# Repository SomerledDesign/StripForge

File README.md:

# StripForge

**Lay out stripboard (Veroboard) circuits in KiCad with real footprints and a live netlist, and get a normal `.kicad_pcb` whose copper is the strips.**

> **Beta (0.3.0).** KiCad 10 only. So far it has been tested on one real board (an ATtiny10
> programming fixture on a 24 × 56 hole stripboard). It works well there, but expect rough
> edges on other boards. Keep backups, check the DRC, and please report what you find.

## Why

Stripboard is still the quickest way to build a one-off circuit you can solder, but laying it out
usually means leaving KiCad for a separate app with its own parts and its own idea of the circuit.
Then the schematic and the build drift apart.

StripForge keeps the whole job inside KiCad:

- **Real KiCad footprints.** It uses the parts from your project, not a second parts library.
- **A live netlist.** The schematic stays the source of truth, and KiCad's schematic-parity check
  keeps the board honest.
- **A normal `.kicad_pcb` as output.** The copper is stripboard strips on B.Cu instead of routed
  tracks. You can open, edit, DRC and plot it like any other board.
- **A printable build sheet.** The copper side mirrored the way you hold the board to cut it, with
  every cut, link and part in checklists.

## What it does

1. **Snaps parts to the grid.** Place the through-hole parts roughly on a 2.54 mm (0.1") grid.
   StripForge snaps each footprint to the nearest holes and logs anything that is off.
2. **Splits the strips by net.** Wherever two nets would share a strip, it cuts the strip. A cut is
   a real gap in the copper plus a `CUT` marker you can see and move.
3. **Adds wire links.** Pieces of one net on different strips are joined with wire links (`W1`,
   `W2`, …), placed on their holes. Links are also added to the schematic, so the two stay in
   sync.
4. **Checks the result with KiCad's DRC**, including schematic parity: a strip carrying two nets, a
   missing link or an extra cut shows up as an error.
5. **Writes a build sheet** (HTML, and PDF when Chrome is installed).

| KiCad's copper layer after Build strips (B.Cu, mirrored) | The build sheet's component side |
|---|---|
|  |  |

The full design is in [Sketch.md](Sketch.md).

## Install

StripForge is a KiCad 10 **IPC plugin**. It is not in KiCad's official Plugin and Content Manager
(PCM) yet.

1. KiCad > Preferences > Plugins: tick **Enable KiCad API**, and check that the Python interpreter
   is KiCad's own (the default on macOS).
2. Build both packages with `python tools/make_pcm_zip.py` (they land in `dist/`), or take them
   from a release. KiCad's addon guide wants a plugin package and a library package, not one zip
   of both. In the Plugin and Content Manager, click **Install from File…** and install
   `StripForge-libraries-0.3.0-pcm.zip` first, then `StripForge-0.3.0-pcm.zip`:

   StripForge then shows on the **Installed** tab as version 0.3.0:

3. **Restart KiCad.** The first time you open a board, KiCad sets up the plugin's Python
   environment, which takes a minute. The PCB editor toolbar shows one button, **Dialog**. It
   opens the window with the Board and Backup tabs. Analyze, Build strips, Add links, Run DRC,
   Build sheet and Restore last are buttons in that window. The Report wraps long lines.

   The picture below is from 0.2.x, when the toolbar had a button per action. 0.3.0 does not.

4. **Check the footprint and symbol libraries.** KiCad's manual says a library package is added
   to the global tables, and the default nickname prefix is `PCM_`. This was not clicked in KiCad
   here, so look at Preferences > Manage Footprint Libraries and Manage Symbol Libraries. If rows
   appeared, they are named `PCM_StripForge`. Rename each to `StripForge` so it matches the
   `StripForge:Link_*` footprints and the `StripForge:Link` symbol the build writes. If no row
   appeared, add them with nickname `StripForge` and these paths:

   - Footprints: `${KICAD10_3RD_PARTY}/footprints/com_github_somerleddesign_stripforge_libraries/StripForge.pretty`
   - Symbols: `${KICAD10_3RD_PARTY}/symbols/com_github_somerleddesign_stripforge_libraries/StripForge.kicad_sym`
   - 3D models (no library table): `${KICAD10_3RD_PARTY}/3dmodels/com_github_somerleddesign_stripforge_libraries/StripForge.3dshapes`

   Each straight `Link_P*` footprint names the matching `.step` in that 3D folder. The `.wrl` has
   the same name beside it. A new straight link copies the footprint, so it inherits that model.
   Diagonal links and the cut markers have no model. The plugin also keeps a private copy of the
   footprints so it can build without the library table. The 3D files themselves are only in the
   libraries package. **Update Footprints from Library**, the 3D viewer, and placing a link by
   hand use the library-table row.

To install by hand instead, copy the *contents* of the plugin zip's `plugins/` folder to
`~/Documents/KiCad/10.0/3rdparty/plugins/com_github_somerleddesign_stripforge/` (macOS; on Linux
`~/.local/share/kicad/10.0/3rdparty/plugins/`, on Windows
`Documents\KiCad\10.0\3rdparty\plugins\`). From the libraries zip, copy
`footprints/StripForge.pretty` to
`.../3rdparty/footprints/com_github_somerleddesign_stripforge_libraries/StripForge.pretty`,
`symbols/StripForge.kicad_sym` to
`.../3rdparty/symbols/com_github_somerleddesign_stripforge_libraries/StripForge.kicad_sym`, and
`3dmodels/StripForge.3dshapes` to
`.../3rdparty/3dmodels/com_github_somerleddesign_stripforge_libraries/StripForge.3dshapes`.
Add the footprint and symbol libraries with nickname `StripForge`. To update, install both new
zips the same way and restart KiCad. If a button does nothing, try Preferences > Plugins >
**Recreate Plugin Environment**.

### If the buttons don't appear (Linux)

On Debian and Ubuntu, KiCad builds the plugin's Python environment with the system Python, which
needs the `python3-venv` package. If that package was missing the first time KiCad tried, it leaves
a half-built environment with no pip, and it keeps reusing it even after you install
`python3-venv`. KiCad prints no error for this, and StripForge never shows up. To fix it:

1. Close KiCad.
2. Install the venv package: `sudo apt install python3-venv`.
3. Delete the broken environment:
   `rm -rf ~/.cache/kicad/10.0/python-environments/com.github.somerleddesign.stripforge`
4. Open the PCB editor again and give it a few seconds to install. The Dialog button appears at the
   right end of the top toolbar.

(The folder is `~/.cache/kicad/10.0/python-environments/` on a standard Linux install; check the
exact name and case with `ls ~/.cache | grep -i kicad` if yours differs. On macOS it is
`~/Library/Caches/KiCad/10.0/python-environments/com.github.somerleddesign.stripforge`; macOS
file names are case-insensitive, so the case doesn't matter there.)

### NixOS, or no dialogs (only status-bar warnings)

StripForge's dialogs need wxPython in the plugin's environment. On NixOS (and any Python without
wxPython) the buttons run but every message only reaches the PCB editor's status-bar warnings; the
full report is still in `stripforge/<Project>-stripforge.log`, and Build strips refuses to
write into the board without a dialog to confirm it. To fix it, set Preferences > Plugins >
**Python interpreter** to a Python that has wxPython (on NixOS, one whose packages include
`wxpython`), then **Recreate Plugin Environment** and restart KiCad.

StripForge isn't listed under Tools > External Plugins, because that menu is for the older SWIG
plugins; the Dialog toolbar button is where it lives. If it still doesn't load, start the PCB editor from
a terminal with `KICAD_ENABLE_WXTRACE=1 WXTRACE=KICAD_API pcbnew` and look at the lines starting
with `Manager:`.

## Using it

Open your project from the KiCad project manager (not the board file on its own, or F8 won't
work), then open the board. **Draw the board outline first**: on the Edge.Cuts layer, draw a
rectangle the size of your stripboard (StripForge derives the hole grid from it, unless
`stripboard.toml` sets `origin_mm`, `rows` and `cols`; without either it refuses before saving
anything). Place the parts on the stripboard's hole grid (a 2.54 mm grid with its origin on a hole
helps); the rest is StripForge's job. Every action also writes its report to
`stripforge/<Project>-stripforge.log` (see **Where StripForge puts its files** below), so if a
button seems to do nothing, look there.

1. **Save the board** (Cmd+S / Ctrl+S), then click **Build strips**. StripForge makes a save point,
   writes the strip copper, the cuts and the wire links into it, and reloads it. The report lists
   every link, anything it couldn't do, and the save point it made. If KiCad says it is busy, press Esc,
   save and click again.

2. **Tools > Update Footprints from Library** (select all footprints, or just the `W` links). This
   gives the links the footprints from the installed library. It matters after you update
   StripForge, e.g. to get 0.2.0's slimmer link outline.
3. Click **Add links to schematic**. It adds a `StripForge:Link` symbol for each `W` link to the
   schematic (and takes out the ones the board no longer has). It makes a save point of the
   sheets it changes first.

4. **Close the Schematic Editor without saving, and reopen it.** It doesn't reload a file changed on
   disk, and saving would undo step 3.
5. Press **F8** (Update PCB from Schematic) in the board. The links match by path, so nothing moves
   and nothing is duplicated.
6. Click **Run DRC**. "shorts 0" and "unconnected 0" is what you want. The report sorts real
   problems from the noise every stripboard has (dead strip ends, for example).

7. Click **Build sheet**. It writes `stripforge/<Project>-stripforge.sheet.html` (and `.pdf` with Chrome) and
   opens it. Print it, cut the strips from the copper-side view, then fit the links and parts.
   Or keep the HTML open on the bench: click a row to tick it off (see **Ticking it off in the
   browser** below).

Changed something? Move parts, cut markers or links and click **Build strips** again: StripForge
keeps your cuts and links and fills in the rest. Then repeat steps 3 to 7. Didn't like the result?
Click **Restore last** (below).

| Build sheet, page 1: the copper side, mirrored | Build sheet: checklists in build order |
|---|---|
|  |  |

### Restore last: your save points

Think of it like a text adventure: before StripForge does anything to your files, it saves the
game. **Build strips** and **Add links to schematic** each make a *save point* first, a zip of
every file they are about to write. If a build went somewhere you didn't want to go, click
**StripForge: Restore last**: each click steps back one save point and you respawn there.

- Restore last removes StripForge's work since that save (the built board, the link lists, the
  link symbols it added to the schematic), puts the saved files back under their own names, and
  reloads the board in the PCB editor. It asks first; unsaved changes in the open board are lost.
- Press it again to step to the next earlier save point, through to the **first** one: the board
  from before StripForge added strips, holes and tracks. One more press reports that there is
  nothing earlier and does not change the board or the zips.
- Before it replaces anything it writes a safety copy,
  `<Project>-stripforge-safety-YYYY-MM-DD_HHMMSS.zip`, in the same folder. That copy is kept.
  The next Restore last does not load it (so the button cannot toggle). `stripforge restore
  <board> --list` shows it; `--backup <zip>` still loads one zip you name.
- If schematic sheets were restored, close the Schematic Editor without saving and reopen it.
- Save points are new files every time, named
  `<Project>-stripforge-YYYY-MM-DD_HHMMSS.zip`; nothing is ever renamed (renames make Dropbox and
  friends create "conflicted copies"). `backup_policy = "move"` (the default) keeps every save
  point. `backup_policy = "retention"` is opt-in: then `backup_keep = N` keeps the newest N
  (`0` still keeps all). A `backup_keep` number on its own does not delete.
- The build sheet isn't a save point; when it changes, the old HTML/PDF are copied into the
  backups folder as `<Project>-stripforge.sheet-YYYY-MM-DD_HHMMSS.html` / `.pdf`.

### Where StripForge puts its files

Everything StripForge writes goes into one `stripforge/` folder next to your `.kicad_pro`
(`${KIPRJMOD}`), named after the project:

```
LoadMan/
  LoadMan.kicad_pro
  LoadMan.kicad_sch
  LoadMan.kicad_pcb               <- Build strips builds into the board itself
  LoadMan.kicad_dru               <- the StripForge DRC rules (KiCad needs them here)
  stripforge/
    stripboard.toml               <- your config (or stripboard.toml next to the .kicad_pro)
    LoadMan-stripforge.links.json   .links.csv   .links.txt
    LoadMan-stripforge.sheet.html   .sheet.pdf   .sheet.copper.svg   .sheet.cuts.csv ...
    LoadMan-stripforge.log
    LoadMan-stripforge.kicad_pcb  <- only with output = "separate"
    LoadMan-stripforge-backups/
      LoadMan-stripforge-2026-10-26_143012.zip   <- save points (Restore last)
```

`output_dir` and `backup_dir` in the config move these folders; both are relative to the project
folder (absolute paths and `..` are refused). Files from StripForge 0.2.x next to the board
(`<name>-pre-stripbuild*.kicad_pcb`, `<name>-stripforge.links.*`, ...) are left where they are;
the build report lists them so you can tidy up.

**Git:** [`plugins/templates/project.gitignore`](plugins/templates/project.gitignore) (also in
the installed plugin's folder) is a `.gitignore` for a KiCad + StripForge project: it ignores the
backups folders, lock files, `*.kicad_prl`, `*.bak`, `fp-info-cache` and `.DS_Store`. Copy it into
your project as `.gitignore`.

### The config file

StripForge reads `stripforge/stripboard.toml`, else `stripboard.toml` next to the board, else the
only other `.toml` there (e.g. `X56.toml`). Without one it takes the grid from the board outline. The options most people need:

```toml
rows = 24                    # strips (A..X)
cols = 56                    # holes along each strip
origin_mm = [51.27, 51.27]   # the centre of hole A1 in the board file
strip_width_mm = 1.8         # measure your board
diagonal_links = false       # the default; true: allow diagonal links when nothing straight fits
max_diagonal_shift = 1       # with diagonal_links: at most this many holes sideways
bus_strips = true            # join two pieces through a spare bare strip
max_link_mm = 81.28          # the longest link (32 holes)
knife_cuts = ["SW2"]         # parts with big pads: cut between holes, not at a hole
slotted = ["BT1"]            # parts whose pins need a hole filed longer
skip = ["SW3"]               # parts that are not on the stripboard
backup_keep = 0              # how many save points to keep (0 = all)

[bend]                       # parts whose legs you can bend onto the holes (mm off)
SW2 = 0.16

[drc]                        # DRC items you accept
ignore = ["silk_overlap"]
```

[`examples/x56.toml`](examples/x56.toml) has every option with comments; the reference below
explains each one.

### Tips

- **Move `CUT` markers, not strip copper.** The strip tracks are redrawn from the markers on every
  build. Drag a marker to another hole (or between two holes) and build again. Don't delete,
  drag or route strip tracks by hand.
- **Don't route copper.** StripForge refuses a board with tracks or vias it didn't draw (apart from
  strip tracks, which it replaces).
- **Keep the link length.** A link footprint has a fixed length (`Link_P7.62`: 3 holes apart). If you
  move a link so it spans a different distance, change its footprint to the matching
  `StripForge:Link_P<mm>` (2.54 mm per hole).
- **Never put a link on a cut.** A wire in a cut hole has no copper to solder to. If you do,
  StripForge drops the cut and warns you, and cuts the strip elsewhere only if two nets would
  short (if the cut is needed exactly there, it keeps the cut and doesn't use the link).
- **Diagonal links: your choice.** They are off by default (`diagonal_links = false`), because
  straight links are easier to fit and check: a net that would need one is joined through a spare
  strip (two straight links) or reported. The report then says when a diagonal would have joined
  it and which setting to change. With `diagonal_links = true` a link may drop to another strip and
  move at most one hole along it; raise `max_diagonal_shift` for longer diagonals.
- **Read the build report.** Anything StripForge couldn't join is listed with its pieces: move or
  turn a part so they come closer, or free some holes.

*A built board up close: the `CUT85`/`CUT86` markers are the cuts (move these, not the copper) and
`W37`/`W38` are wire links, ringed so they stand out.*

## Status

**Beta, 0.3.0.** StripForge runs inside KiCad 10's PCB editor (the IPC plugin above) and as a
command line (`stripforge analyze | snap | build | link-symbols | drc | sheet`, see
[Development](#development)). Tested with KiCad 10.0.4 on macOS, on one real board. Not yet in the
official PCM.

The plugin does its work on the saved board file with a file backend plus `kicad-cli`, both
headless, and uses KiCad's IPC API only to find, save and reload the open board. The SWIG `pcbnew`
API is avoided because KiCad 11 removes it. Python 3.9+ (KiCad 10's bundled Python on macOS is
3.9).

## Roadmap

| Milestone | Scope |
|---|---|
| **M0: Foundations** | Repo and CI; lossless S-expression round-trip on a KiCad 10 board; netlist parser; fixture intake; strip, cut-marker and link-footprint specs; a first `.kicad_dru`; verify every open question against a real KiCad 10 install. |
| **M1: Model and splitting** | Pure-Python grid snap, strip model, cut placement, net per piece, link proposals and validation, with unit tests and a JSON plan output. |
| **M2: Board output and DRC** | File-backend `.kicad_pcb` writer, `kicad-cli` DRC wrapper and classifier, the two-pass link flow, and mutation tests proving DRC guards the layout. |
| **M3: Build sheet and IPC** | Mirrored SVG/PDF build sheet with cut and link lists; the KiCad plugin. Done in 0.1.0; 0.2.0 is the first beta. |
| **M4** | In 0.3.0: fail loudly (0.2.1); save-point zips and Restore last walking back to the first save; diagonal links off by default; backup policy defaults to move and never deletes unless retention is chosen. The toolbar has one button, Dialog. That window edits settings, the raw stripboard.toml, and the backup policy, and runs the actions. See [Sketch.md](Sketch.md) §7. |
| **Later** | More boards tested, pre-drilled mounting holes, the official PCM. |

## Reference

The rest of this README is the detailed reference: every action, option and report in full.

### The plugin's actions

- **StripForge: Analyze**: a read-only report: snap, cuts, links needed, slot jobs, hints.
- **StripForge: Build strips**: builds **in the open board itself** (`<name>.kicad_pcb`, the
  project's own board, so F8 keeps working), after saving it and making a save point (a zip in
  `stripforge/<Project>-stripforge-backups/`). With
  `place_links = true` (the default) the `W` link footprints are placed on their holes too. It
  then reloads the board in the PCB editor. Writes `<name>.kicad_dru` next to it and the link lists
  (`stripforge/<Project>-stripforge.links.*`). See **Where the build goes** below;
  `output = "separate"` writes `stripforge/<Project>-stripforge.kicad_pcb` instead.
- **StripForge: Add links to schematic**: writes a `StripForge:Link` symbol for every placed `W`
  footprint into the project's schematic, in place (see **Links from the board to the schematic**
  below). A save point of the changed sheets is made first. **Then close the Schematic Editor without saving and reopen
  it**: it does not reload a file changed on disk.
- **StripForge: Run DRC**: kicad-cli DRC with schematic parity on the built board, classified.
- **StripForge: Build sheet**: writes `stripforge/<Project>-stripforge.sheet.html` (and `.pdf` if
  Chrome is installed) and opens it in the browser.
- **StripForge: Restore last**: steps back one save point and reloads the board, repeating back
  to the first save point (see **Restore last** above); `stripforge restore` on the command line.
- **StripForge: Dialog**: the shared window. It shows the saved settings, lets you set
  `backup_policy` (`move` or `retention`) and `backup_keep`, and runs the actions above through
  the same code as their buttons. Saving the policy does not delete a save point. The other
  buttons remain.

Each action offers to save the board first, because StripForge reads the saved file:

 It uses
`stripforge/stripboard.toml` or `stripboard.toml` next to the board if there is one. Without it,
it uses the only other `*.toml` there (e.g. `X56.toml`) if that is a valid StripForge config, and says so in the
report; with several, or none, it derives the grid from the Edge.Cuts outline. If
`<project>.kicad_sch` is there, it exports a fresh netlist with kicad-cli to cross-check pad nets.
Results appear in a dialog ("Show in Finder", "Copy report"). If a button does nothing, see the
status-bar warnings or Preferences > Plugins > "Recreate Plugin Environment". To uninstall a hand
install, delete its folder. Manual test steps: [docs/KICAD-PLUGIN-TEST.md](docs/KICAD-PLUGIN-TEST.md).

The footprint library, the `StripForge:Link` symbol, and the straight `Link_P*` 3D models are the
libraries package, installed separately from the plugin (see [Install](#install)). A new straight
link copies the footprint, so it inherits that footprint's model. `stripforge link-symbols` also
embeds the symbol in the schematic.

### Circuit acceptance

The acceptance circuit is Kevin's **LedSwitch25** project, the zip
[tests/fixtures/ledswitch25/LedSwitch25-kicad.zip](tests/fixtures/ledswitch25/LedSwitch25-kicad.zip)
(25819 bytes, sha256 `4b6641a48ca721d24437f30cdbdc85c4168e3854628f75778c3d98b421883e3c`).
Check the hash, extract a new copy, and do not edit or re-zip the archive. It is Kevin's
2026-11-08 board with only `rows = 12` and `cols = 12` changed. The previous zip is
`LedSwitch25-kicad-2026-11-07-2158.zip` in that same folder and is not current. The toml
comments still say 25 by 25, a 63.5 mm outline, and origin (1.27, 1.27) mm. Those comments are
Kevin's and were left as archived. The settings are 12 by 12, origin `[129.54, 104.14]`,
`output = "in_place"`, `link_lead_allowance_in = 0.15`, `backup_policy = "move"`,
`backup_keep = 0`. Edge.Cuts is a 33.020 mm (1.3 in) square, from (127.00, 101.60) to
(160.02, 134.62). The first hole is 2.54 mm in from the edges, and the last hole has the same
100 mil margin on the far sides. An older LedSwitch zip, including a 9022-byte copy, is not
this archive. SW1 is on the hole grid and the archived build does not use a `[bend]` override.

The **ATtiny10 TPI** boards stay unit fixtures (22 real parts in
[examples/tpi-fixture](examples/tpi-fixture/); the 25-part M1 board is frozen in
`tests/fixtures/tpi-m1/`). They are not the acceptance circuit.

### Development

```sh
python -m venv .venv && source .venv/bin/activate
pip install -e '.[dev]'
stripforge analyze examples/tpi-fixture/ATtiny10_TPI_Fixture.kicad_pcb \
    --netlist examples/tpi-fixture/ATtiny10_TPI_Fixture.net      # add --json for machine output
stripforge analyze <board>.kicad_pcb --config examples/x56.toml  # Kevin's X56 board (A1-X56)
stripforge snap <board>.kicad_pcb -o <out>.kicad_pcb   # move parts by their best-fit shift (dry run without -o)
stripforge build <board>.kicad_pcb --netlist <board>.net --config examples/x56.toml   # in place, backup first
stripforge build <board>.kicad_pcb --separate        # or -o <out>.kicad_pcb: a new file, board untouched
stripforge drc <board>.kicad_pcb                     # kicad-cli DRC + parity against <board>.kicad_sch
stripforge sheet <out>.kicad_pcb --netlist <board>.net --config examples/x56.toml -o <out>.sheet.html
python tools/make_pcm_zip.py   # the KiCad PCM package in dist/
stripforge --help      # plan is still a stub
ruff check . && ruff format --check .
pytest
```

### Building a board: `stripforge build` and the two-pass link flow

`stripforge build <board> [--netlist <net>] [--config <toml>] [--separate | -o <out.kicad_pcb>]`
snaps the parts (as `snap` does), splits the strips by net and writes the result (see **Where the
build goes** below for which file):

- **strips**: one `B.Cu` track per pair of neighbouring holes, hole centre to hole centre,
  `strip_width_mm` wide, on the piece's net. Uncut bare strip is written as copper with no net (it
  is physically there; KiCad only calls it `track_dangling`, which `stripforge drc` filters);
- **cuts**: a real gap in the copper (a hole cut leaves no copper touching the hole; a knife cut
  removes the track between two holes) plus a `StripForge:CUT_Hole` / `StripForge:CUT_Knife`
  marker footprint on `User.1` (refs `CUT1`…, board-only, not in the BOM or position files). The
  markers are embedded in the board, so it loads and DRCs without the StripForge library configured;
- **holes**: every free stripboard hole is drawn (one board-only `SF_HOLES_<strip>` footprint per
  strip with a plated pad per hole, on that strip's net, on `B.Cu` only), so the built board looks
  like the real board in pcbnew and the 3D viewer. Hole cuts are drawn as bare (non-plated) holes;
  holes under part pins and link pads take the part's pad instead. `draw_holes = false` turns this
  off, `hole_drill_mm` (default 1.0) sets the drill;
- **links**: see below;
- next to the built board: `<name>.kicad_dru` (a copy of `rules/stripforge.kicad_dru`, which
  `kicad-cli` and pcbnew pick up automatically; a different `.kicad_dru` that was already there is
  kept in the save point), and in `stripforge/` the link proposal as
  `<Project>-stripforge.links.json`, `.links.csv` and `.links.txt`.

**Where the build goes: `output`.**

| toml key | values | default |
|---|---|---|
| `output` | `"in_place"`: build into the board itself (`<name>.kicad_pcb`) · `"separate"`: write `stripforge/<Project>-stripforge.kicad_pcb` and leave the board alone | `"in_place"` |
| `backup_policy` | `"move"`: keep every save point. `"retention"`: opt in to deleting older ones | `"move"` |
| `backup_keep` | with `"retention"`, how many save points to keep (the newest N). `0` keeps every one. Ignored while policy is `"move"` | `0` |
| `output_dir` | StripForge's folder, relative to the project folder | `"stripforge"` |
| `backup_dir` | the save points' folder, relative to the project folder | `"<output_dir>/<Project>-stripforge-backups"` |

In place is the default because F8 (Update PCB from Schematic) only works in the project's own
board, opened from the KiCad project manager: in a separate file pcbnew says "PCB editor is opened
in stand-alone mode".

**Save points.** Before every build, just before anything is written, StripForge zips the files
the build is about to write (the board, its `.kicad_dru`, the link lists) into a new
`<Project>-stripforge-YYYY-MM-DD_HHMMSS.zip` in the backups folder, with a small
`stripforge-backup.json` listing them and the ones that didn't exist yet. Nothing is ever renamed
or overwritten (two builds in the same second get `-2`, `-3`, ...); if the zip can't be written the
build stops before touching anything. With `backup_policy = "retention"` and `backup_keep = N`
(N at least 1) the oldest zips are then deleted so N remain. The default policy `"move"`, and a
file that never sets `backup_policy`, does not delete, even if `backup_keep` is set. **To undo
builds:** `stripforge restore <board>` (the plugin's Restore last) steps back one save point
each time, until the first. It deletes the files that didn't exist at that save point and unzips
the rest under their own names, after writing a safety copy of the current board. At the first
save point the next run changes nothing. `--list` shows the save points, `--backup <zip>` loads
the one you name.
On the command line `--separate` (or `-o <other file>`) overrides the toml for one run;
`-o <board> --in-place` is the same as the default. A `-stripforge` board (from
`output = "separate"`) is always rebuilt in place.

The input must be the placement board: a track or via StripForge did not write is refused. Building
again from a StripForge output removes its own strips and cut markers first and rewrites them (a
strip track re-drawn by hand along a strip row, which lost StripForge's uuid, is replaced too, with a
warning; any other track, a via or F.Cu copper is still refused); the output is deterministic (same input, same bytes). Parts outside the Edge.Cuts outline are reported,
and copper is only written for holes inside the outline.

**Pass 1.** For every net split over several strip pieces, StripForge proposes wire links like a
minimum spanning tree: fewest and shortest links, from **any free hole** of one piece to any free
hole of another (every grid hole counts, not only footprint holes; never a cut, a pad or another
link's hole). In order of preference a link runs:

1. straight down a column (`StripForge:Link_P2.54` … `Link_P81.28`, 1–32 pitches); a cut may slide
   (or a piece extend) within its gap to give both pieces a free hole in the same column;
2. along a strip, bridging a cut (rare: two pieces of one net on one strip are only split when a
   different-net pin sits between them, and a wire can't run over that pin);
3. as two straight links meeting on a **bus strip** (`bus_strips`, default on): a piece of unused
   bare strip that the net takes over, with a straight drop from each piece (a cut may slide to line
   one up); hole cuts isolate the bus from the rest of that strip where that leaves a useful
   remainder (the report says "hole cut at R5 isolates a bus strip");
4. only when nothing straight fits and you turned them on, on a diagonal (`diagonal_links`, default
   **off**; at most `max_diagonal_shift` holes sideways, default 1), rotated: a
   `Link_P*` when the length is a whole number of pitches (3-4-5 and friends), otherwise an
   off-pitch `Link_D<mm>` (`Link_D3.59` for a 1x1 offset … `Link_D81.16`; 305 footprints in the
   library; `off_pitch_links = false` keeps to whole-pitch diagonals).

| toml key | what it does | default |
|---|---|---|
| `diagonal_links` | allow diagonal links when nothing straight fits | `false` |
| `max_diagonal_shift` | with `diagonal_links`: how many holes a diagonal may move along the strip it drops to (1 to 32) | `1` |
| `off_pitch_links` | with `diagonal_links`: also use the off-pitch `Link_D*` (`false`: whole-pitch diagonals only, which need a shift of 3 or more) | `true` |
| `bus_strips` | join two pieces through a spare bare strip | `true` |
| `max_link_mm` | the longest link | `81.28` (32 holes) |

> [!WARNING]
> With `off_pitch_links = false`, a `max_diagonal_shift` of 1 or 2 rules out **every** diagonal:
> the shortest whole-pitch diagonal (3-4-5) needs a shift of 3. Use `max_diagonal_shift = 3` or
> more, or leave `off_pitch_links = true`.

When a net is left unjoined and a diagonal (or a longer one than `max_diagonal_shift` allows) would
have joined it, the report says so and names the setting, e.g. "It can't be joined without a
diagonal link (shifting 4 holes along a strip): set diagonal_links = true in the config with
max_diagonal_shift = 4". (StripForge plans once more with any diagonal allowed to find out; a net
that only gets room because *other* nets use diagonals is reported that way.)

A straight link always beats a diagonal, however long; then fewer crossings under parts, fewer
moved cuts, shorter wire.

Rules for every link: no longer than `max_link_mm` (default 81.28 mm = 32 pitches); never crossing
or touching another link; never passing over (within 0.9 mm of) a part pin or another link's end,
since bare wire would short to it; part courtyards avoided where possible (a wire may run under a
part, reported). The report lists each link, with the rotation for diagonals:

```
W4    D12 -> J12  (0.6")   StripForge:Link_P15.24   GND
W19   J16 -> T16  (1.0")   StripForge:Link_P25.40   +5V_T  (to bus strip T)
```

Each link's length is in inches, **pad-to-pad** (pitches × 0.1"; a diagonal's real length to
0.01"). After the list comes a **link cut list**, one row per length, shortest first, so you can
cut and bend every link of one length and fit them in one go:

```
Link cut list (pad-to-pad): 14 length(s), 34 link(s)
   Length  Qty  Links
     0.1"    8  W3, W15, W18, W21, W24, W26, W31, W33
     0.2"    5  W2, W11, W12, W13, W14
  ...
  Note: Lengths are the pad-to-pad span only. Remember to add wire for both legs: ...
```

The lengths are the span between the two holes only: add wire for both legs through the board, the
bend and the solder or clinch (roughly 0.1"–0.2" a leg). `link_lead_allowance_in = 0.15` (inches a
leg, default 0 = off) adds a **Cut** column: pad-to-pad + 2 × allowance. The build sheet has the
same chart (with checkboxes) under the wire-link list.

**Lead-stretch suggestions** (report only, on by default): after the plan, StripForge checks
whether a longer lead on a leaded two-pin part (R, C, D, L, F) could take the place of a link: the
part keeps one pin where it is and its pin on the link's net moves to a free hole on the far side,
so that `W` need not go into the schematic. It is suggested only when the net stays connected
without the link, the new hole is free and already on that net (no new cut, no short, not beside a
`knife_cuts` part's big pad), the new line crosses no link, passes over no lead and runs under no
part it didn't already, and the span grows by at most `max_pitches` (axial, default 6) or
`radial_max_pitches` (legged caps, LEDs, fuses; default 2). Nothing is moved: change the part's
footprint (longer pitch or rotated) so the pin lands on the new hole, leave the link out and build
again.

```toml
[stretch]
# enabled = true            # false: no suggestions
# max_pitches = 6           # axial parts: how much longer the span may get
# radial_max_pitches = 2    # radial parts
# skip = ["C1"]             # never stretch these
# allow_under_parts = false # true: also suggest a new line under another part
```

```
Lead stretches: 1 suggestion(s), 1 link(s) fewer (report only; nothing moved)
  replaces W26: move R2 pin 2 from O10 to P10 (R2.1 stays at K10; span 4 -> 5 pitches, +1)
```

Add them to the schematic: one 2-pin link per line, the generic `StripForge:Link` symbol from
`symbols/StripForge.kicad_sym` (or `Jumper:Jumper_2_Bridged`, or a 0 Ω resistor), Reference `W4`,
Footprint `StripForge:Link_P15.24`, both pins wired to the net (`GND`). Or let StripForge do it:
see **Links from the board to the schematic** below.
Then press F8 (Update PCB from Schematic) in the same board. `<name>-stripforge.links.txt` has the
full list and these steps. A
net that still can't be joined is an error in the report, naming its pieces: move or rotate a part
so they come closer, or free some holes.

**Pass 2.** Build again in the board that now has the `W` footprints (anywhere on the board): each
`W` is matched by reference and net to the proposal and placed on its two holes (pad 1 on the upper
hole; a straight-down link at 0°, a diagonal or along-the-strip link rotated so pad 2 lands on
its hole). Missing, extra, wrong-footprint or wrong-net `W`
parts are reported. The `W` parts are not treated as components, so the strips and cuts don't
change.

Exit codes: 0 complete (every net joined, every link placed), 1 incomplete (links still to add or
place, unlinkable nets, rejected parts), 2 refused (bad input, conflicts, output = input).

**Links from the board to the schematic: `place_links` and `stripforge link-symbols`.** Instead
of adding the `W` symbols by hand, let the board lead:

```sh
stripforge build MyProject.kicad_pcb --config X56.toml            # place_links = true by default
stripforge link-symbols MyProject.kicad_pcb --in-place             # reads/edits MyProject.kicad_sch
#   a save point (zip) of the changed sheets is made first; stripforge restore undoes it
#   or --out-dir DIR: a copy of the project; --schematic <root .kicad_sch> picks another schematic
```

`place_links = true` (the default; `--no-place-links` or `place_links = false` turns it off) places every proposed link's
`Link_P*`/`Link_D*` footprint on its holes in the first build, both pads on the link's net, so there
are no ratsnest lines left to wire. Each is locked (F8's "Delete footprints with no symbols" won't
remove it), has Value `Link`, and carries the schematic path of the symbol that `link-symbols`
will write. `link-symbols` then adds one `StripForge:Link` symbol per `W` footprint the schematic
lacks: its reference, its Footprint field (`StripForge:Link_P27.94`), and a label with the net's
name on both pins. A `/Sheet/NAME` net gets local `NAME` labels on that sheet. Any other net
(`GND`, a global label) gets global labels. An unnamed net (`Net-(SW2B-B)`) also gets a global
label of the same name on one of its existing pins, so it keeps its name. The symbols are set out
in a grid right of the drawing, under a note, and the paper is enlarged if they don't fit. The
copy (`--out-dir`) holds every sheet, the project file, the library tables (with `${KIPRJMOD}`
pointing back at the original project) and the board under the project's name, ready for
`kicad-cli` netlist, ERC and `stripforge drc` parity. Then press F8: the symbols and footprints
match by path, so nothing moves and no second copy appears. KiCad's own Tools > Update Schematic
from PCB can't do this step, because it only updates symbols that already exist. For a footprint
with no symbol it reports "Cannot find symbol for footprint" (eeschema `backannotate.cpp`, KiCad
10.0). Until the symbols are in, `stripforge drc` counts each `W` as a parity `extra_footprint`
and says to run `link-symbols`. With `place_links` on, don't also add the `W` symbols by hand: F8
would bring in a second footprint for each link. The `StripForge:Link` symbol definition is
embedded in the schematic (`lib_symbols`), so no sym-lib-table entry is needed (ERC stays clean);
add the `StripForge` library by hand only if you want to place links yourself.

**W symbols that are already in the schematic** (for example placed by hand, with footprints from
Update Schematic from PCB but no nets) are kept where they are and never duplicated:
- **Bare pins:** each pin with nothing on it gets a net label (local or global, as above).
- **Path:** the symbol's uuid is set to the one its placed footprint's path names, so F8 matches
  the two by path instead of adding a second footprint. If the symbol sits on another sheet than
  that path, the report warns instead.
- **Footprint:** an empty or different Footprint field is set to the board's.
- **Conflicts:** a pin already wired to a label of another net is left unchanged, together with
  the rest of that symbol, and reported as a `CONFLICT` to fix in the schematic or on the board. The W footprints
are embedded in the board, and F8 leaves a matched footprint alone when its library ID is the
same, so the footprint library isn't needed for F8 either.

**The same flow in KiCad** (open the project in the KiCad project manager, then its board):
1. Click **Build strips**. The board is saved, a save point is made,
   built in place with the `W` links placed on their holes, and reloaded.
2. Click **Add links to schematic**. It adds the `W` symbols to the schematic, and the report
   lists them with the save point. If the Schematic Editor is open, close it without saving
   and reopen it.
3. Optionally press F8 in the same board. The symbols and the placed footprints match by path, so
   nothing moves and nothing is duplicated.
4. Click **Run DRC** (unconnected should be 0, apart from any net the report calls unlinkable),
   then **Build sheet**.

With `place_links = false`: click Build strips, add the listed links to the schematic yourself,
press F8 in the same board, then click Build strips again to place them.

### Moving cuts and links yourself

StripForge's plan is a starting point: you can move any cut or link, and building again keeps what
you did ("locked") and only fills in what is still unjoined. Two ways:

**In the built board, in pcbnew:**
1. Open the built board (`<name>.kicad_pcb` after an in-place build). Cut markers are the `CUT…` footprints on `User.1`; links are the `W…`
   footprints (after pass 2).
2. Move a cut: drag its `CUT…` marker onto another hole (a `CUT_Hole`) or between two holes (a
   `CUT_Knife`). **Only move the marker; leave the strip copper alone.** The strip tracks are
   regenerated from the markers on every build, so after **Build strips** the gap is where the
   marker is and the old gap is filled. Don't delete, drag or route strip tracks by hand: the
   interactive router won't join copper of two different nets (the old gap has one net either
   side), and any strip track you do draw is thrown away and redrawn on the next build. Add a cut: place a `StripForge:CUT_Hole` or `CUT_Knife` footprint (any ref, e.g.
   `CUT99`). Remove a cut: delete its marker (if that would short two nets, StripForge puts the cut
   back and says so).
3. Move a link: drag the `W` footprint so both pads sit on holes (grid 2.54 mm; rotate with R for
   an along-the-strip or diagonal link). A link has a fixed length: to make it longer or shorter,
   change its footprint to the right `StripForge:Link_P<mm>` (Link_P2.54 per pitch; `Link_D*` for
   off-pitch diagonals), or change it in the schematic and press F8. A link dropped in from the
   library (reference `REF**`) gets the next free `W` number and its net on the next build. If a
   link end lands on a hole-cut marker, the link wins: the marker is dropped with a warning, and
   the strip is cut elsewhere only where two nets would otherwise short. A link the build can't use
   (a pin in its hole, two nets shorted) keeps its name and is reported as not used, not placed.
   To remove a link, delete its `W` footprint and build again. A link that no longer joins anything
   (one end on bare strip no other link reaches, e.g. the second leg of an old bus strip) is
   removed by the build itself. Then **Add links to schematic** takes stale W symbols out of the
   schematic (backed up first), so F8 doesn't bring the footprint back.
4. Click **Build strips** with that board open: it is saved, rebuilt **in place** (same file),
   keeping your markers and links where they are, and reloaded (backed up first, like every build).
   The report lists your links as "(yours, kept)", the new ones to add, and any problem.

**In `stripboard.toml`, as text** (easiest; applied on every build, also on the placement board):

```toml
[manual]                         # a table: put it after the top-level keys
links = ["J16-T16", "C42-X42"]   # wire links from hole to hole (any two free holes)
cuts = ["J15", "C34-C35"]        # a hole cut at J15, a knife cut between C34 and C35
no_cut = ["J17"]                 # never cut here (StripForge picks another spot in that gap)
```

Your cut replaces StripForge's cut in the same gap and is never slid. StripForge checks your edits
and warns when: a cut or link lands on a hole with a pin in it (or a link on a cut or a slot's hole);
a link would short two nets or lands on a strip of another net than its schematic net; your links
cross; a missing cut would short two nets (it is put back); a cut splits a net that can't then be
joined. Rejected links are reported, and their `W` reference is reused for the link that replaces
them. `respect_edits = false` ignores the board's markers and links and plans from scratch (the
`[manual]` table still applies). The build sheet marks your cuts and links "(yours)".

### Build sheet: `stripforge sheet`

`stripforge sheet <built board> [--netlist <net>] [--config <toml>] -o <out>.html [--png] [--no-pdf]`
writes one self-contained, printable HTML file (Letter landscape, light background, works offline).
When Chrome/Chromium is found (`--chrome`, `$STRIPFORGE_CHROME`, `PATH`, or the macOS app) it
also writes `<out>.pdf`. `--png` adds `<out>.copper.png` / `<out>.component.png` previews. The two
view SVGs and `<out>.cuts.csv` are always written. When the new sheet differs from the one already
there, the old HTML and PDF are first copied into the backups folder as
`<out stem>-YYYY-MM-DD_HHMMSS.html` / `.pdf` (new names each time, limited by `backup_keep`); an
unchanged sheet makes no copy. The sheet has:

1. **Copper side (bottom), MIRRORED:** as seen with the board flipped over to cut (hole 1 on the
   right). It shows cuts (hole ✕, knife bar), solder points, link ends and slot jobs, with strip
   letters and hole numbers on every edge, an A1 corner mark and a 10-hole ruler.
2. **Component side (top):** part outlines, refs, values, pin-1 marks and links drawn as wires.
3. **Checklists in build order** with checkboxes:
   - cuts grouped by strip;
   - slot jobs ("file U16 0.025" (0.635 mm) toward U17 (toward the part centre)");
   - wire links (ref, from, to, length pad-to-pad in inches and holes, footprint, and "diagonal,
     4 across and 3 down", "along the strip" or "to bus strip R"); both views draw every link at
     its real angle; then the **link cut list** (length | qty | links, shortest first, with the
     reminder to add wire for the legs) and any lead-stretch suggestions;
   - parts, low-profile first, with every pin's hole.
4. **Net check:** every net and every hole it must touch, for a continuity meter.
5. **Warnings:** knife cuts, courtyard overlaps, unlinkable nets, links still to add, and a banner
   if the file isn't a (current) StripForge build.

**Ticking it off in the browser.** In the HTML sheet, click a checklist row (or its box) to tick
it: the box fills, the row is struck through except its Status, and the Status says **Cut** (a cut)
or **Installed** (a link or a part). Click again to undo. A "Progress" bar shows how many cuts,
links and parts are done (e.g. "12/34 links"), and **Reset checklist** clears them all. The ticks
are saved in the browser (localStorage), keyed by the board name and a hash of the checklists, so a
refresh, or running Build sheet again on the same build, keeps them; a rebuild that changes a cut,
link or part starts a fresh checklist. Printing the HTML prints the ticks and strike-throughs as
they are. The script is inline (no files or network). The PDF stays a plain printout to tick by
pen: Chrome's print-to-PDF can't make PDF form checkboxes.

Large boards are split across pages.

### DRC: `stripforge drc`

`stripforge drc <board.kicad_pcb> [--no-parity] [--report drc.json] [--json]` runs
`kicad-cli pcb drc --format json --severity-all --schematic-parity` (kicad-cli 10.0.4; found via
`--kicad-cli`, `$KICAD_CLI`, `PATH` or the macOS app bundle) and classifies the result:

- **real problems** (exit 1): shorts, clearance, unconnected items, schematic parity, violations of
  a StripForge (`SF …`) rule, and any other error;
- **filtered, counted** (expected on stripboard): `track_dangling` (dead strip ends), the
  "footprint library not configured" warning (the footprints are embedded), and courtyard/library
  items of the drawn `SF_HOLES_*` hole footprints ("N stripboard-hole item(s)": the holes under
  parts are real holes);
- **reported, not failing**: a `W` link over a part courtyard (a wire can run under a part), and
  other warnings (silk), summarised by type.

**Config filters (`[drc]` in `stripboard.toml`):** pass `--config` (the plugin always does) and
the table's filters apply. Everything they suppress is still counted, one line per type or pair:
`filtered (config): 1 courtyards_overlap J2/C2, 2 pth_inside_courtyard J2/C2, 1 silk_overlap`.

```toml
[drc]
# KiCad 10 DRC type names, suppressed board-wide (a name KiCad doesn't have is warned about)
ignore = ["silk_overlap", "silk_over_copper", "silk_edge_clearance"]
# courtyard overlaps accepted for exactly these reference pairs (order doesn't matter): covers
# courtyards_overlap and pth_/npth_inside_courtyard between the two parts; others still count
allow_overlap = [["J2", "C2"], ["J2", "C3"]]
```

Unknown keys in `[drc]` are an input error (exit 2). The type names are the `type` values in
kicad-cli's JSON report (KiCad 10's list is in `stripforge.config.KICAD_DRC_TYPES`).

Schematic parity needs the `.kicad_sch` (and `.kicad_pro`) next to the board with the same name;
without it kicad-cli skips parity and the report says so. An in-place build keeps that name, so
parity runs against `<name>.kicad_sch` directly. For a `<name>-stripforge.kicad_pcb` board
(`output = "separate"`) `stripforge drc` finds `<name>.kicad_sch` itself (or pass `--schematic`)
and runs on a shadow copy of the project in a temp folder. After pass 1 the unconnected items are
exactly the links still to add; after pass 2 they should be 0. Exit 3 means kicad-cli was not found
(the tests needing it are skipped in CI).

### Slotted parts

Parts whose pins are not on the 2.54 mm grid along a strip (the MPD BH23APC 23A holder, BT1) are
listed in `slotted = ["BT1"]`. Their end holes are filed toward the part centre instead of
rejecting the part. The filing distance is the pad's offset from its hole plus half of how much
longer than wide its drill is: for the BH23APC (oval 1.635 × 1.0 mm slots 0.3175 mm inboard;
slot centres 32.385 mm apart, pins seat 31.75 mm apart) that is **0.025" (0.635 mm)** at each
end. Place the footprint with its origin on a hole; if one end is nearer its hole than the other,
analyze warns, e.g. "BT1 slot offsets 0.000/0.635 mm; shift -0.318 mm along the strip (toward lower
hole numbers) to centre it" (in KiCad: Move Exactly, X -0.3175).

### Bent legs: `[bend]` (the "Beckham tolerance")

Some parts can't sit on the holes but their legs bend far enough to reach them, like Kevin's DPDT
slide switch (SW2): 300 mil pin pitch along a row but 312 mil between the rows. Centred, each row
is 6 mil (0.1524 mm) off its strip, just over `snap_tol_mm` (0.15 mm). List such parts in a `[bend]`
table with the most a leg may be off its hole, in mm (6 mil = 0.1524 mm, 10 mil = 0.254 mm):

```toml
[bend]   # Beckham tolerance: parts whose legs can be bent onto the holes (bend it like Beckham)
SW2 = 0.16
```

- The value replaces `snap_tol_mm` for that part only, in any direction. For a part that is also
  `slotted`, the slot takes the along-strip offset and `[bend]` sets the across-strip tolerance.
- Values must be more than 0 and at most 0.5 mm; above 0.3 mm there is a warning (check the part
  really bends that far). A `[bend]`, `slotted` or `skip` entry for a part that isn't on the board
  is warned about.
- Analyze lists every leg to bend (`bend legs: SW2 [bend] 0.16 mm [pad 1 at C40: 0.152 mm (6.0 mil)
  across the strip; ...]`) and warns that the part was accepted with its bend tolerance. The build
  sheet's parts list says "bend legs up to 0.152 mm (6.0 mil) across the strip to fit the holes".
- `[bend]` parts are placed off the holes on purpose, so the best-fit shift never moves them.
- A rejected part now gets the matching hint: a miss across the strip suggests `[bend]` with a
  value (e.g. `SW2 = 0.16`), a miss along the strip suggests `slotted`, and a part whose pins match
  the pitch but sit off the grid is told how far to move it (KiCad: Move Exactly).

### Big-pad parts: `knife_cuts`

Parts whose pads overhang neighbouring holes (a slide switch's 2.9 mm blade pads, for example) need
knife cuts, not drilled hole cuts, around them: a hole cut next to the pin would drill into the pad.
List them:

```toml
knife_cuts = ["SW2"]
```

Every cut that isolates a pin of a listed part is a knife cut, placed so the hole beside each of
its pins stays on that pin's net (the pad overhangs it). The link planner never slides those cuts
closer. When two pins of different nets are too close to leave a spare hole beside each (one or two
holes apart), the best knife cut is still made and a warning says so: check DRC clearance there.
The build sheet marks them "knife, per SW2 setting". An unknown reference is reported.

### Trim unused strip ends: `trim_pieces`

After the links are planned, every net piece is cut back to its outermost used hole (a pin or a
link end) when that frees at least `trim_min_free` holes (default 4) as bare copper again, free for
other nets and buses:

```toml
# trim_pieces = true
# trim_min_free = 4
```

Hole vs knife follows the usual rules (and `knife_cuts`). When a net is left unjoined, planning is
also tried with the pieces trimmed first (more bare strip for buses) and kept if it joins more.

### Parts off the stripboard: `skip`

`skip = ["SW3", "J9"]` lists parts that are not on the stripboard (panel-mounted, hand-wired). They
are not snapped or rejected, their pads get no strips, and nothing is planned for them. Analyze
warns, per part, which nets must be hand-wired to it, and the build sheet lists them under "Wired
off-board". Nets they share with on-board parts are still split and linked as usual on the
board; the wire to the skipped part is up to you. (`offboard_refs`, the older name, still works;
the two lists are merged.)

### Strip width and the DRC rules

`strip_width_mm` is 1.8 mm (caliper-measured on Kevin's X56 board). The rules in
`rules/stripforge.kicad_dru` are generated for that width: **whenever `strip_width_mm` changes,
regenerate them** with `python rules/gen_dru.py --strip-width <w>`. `stripforge build` warns when
the rules file and the config disagree.

### Hole labels

Copper strips run horizontally. Strips (rows) are letters `A..Z`, then `AA, AB, …, ZZ`
(spreadsheet style); holes along a strip are numbered from 1. The top-left hole (component side) is
`A1`, so `K12` is the 12th hole on the 11th strip. The TPI fixture's 30 × 25 grid runs `A1`–`Y30`.
Reports use labels throughout; the `--json` output also keeps the 0-based `(col, row)`.

```
src/stripforge/
  cli.py          command-line entry (analyze | snap | build | link-symbols | drc | sheet; plan is a stub)
  analyze.py      snap + split report (text or JSON), best-fit moves
  hints.py        placement hints (parts lying along a strip, 90° rotation estimate)
  config.py       stripboard.toml model
  netlist.py      kicad-cli netlist (kicadsexpr) parser
  sexpr.py        S-expression reader/writer (byte-exact for untouched nodes)
  board.py        footprints, pads (absolute positions, rotation) and outline from a .kicad_pcb
  grid.py         2.54 grid, hole labels, per-footprint snap with tolerance and slots
  strips.py       rows -> hole-to-hole segments
  splitter.py     cut placement + net per piece
  links.py        link proposals (pass 1), link reports
  writer.py       stripforge build: strips, cut markers, link placement (pass 2 / place_links)
  linksym.py      stripforge link-symbols: W footprints -> StripForge:Link symbols in the schematic
  resources.py    StripForge footprint library and rules lookup
  validate.py     pure-Python short/open/parity pre-check
  drc.py          kicad-cli pcb drc wrapper + classifier
  buildsheet.py   stripforge sheet: printable HTML/PDF build sheet, view SVGs/PNGs, cuts CSV
  backends/       file (.kicad_pcb), ipc (kipy; stub), swig_fallback (isolated, unused)
plugins/          KiCad 10 IPC plugin: plugin.json, sf_dialog.py, stripforge_plugin.py, icons
symbols/          StripForge.kicad_sym: the generic StripForge:Link symbol (2 passive pins, ref W,
                  value Link, footprint filter Link_*); bundled in the plugin as plugins/symbols/
tools/            make_pcm_zip.py (PCM package), make_icons.py (toolbar icons)
```

### Icon

The StripForge icon is `resources/icon.png`: Kevin's 64 × 64 px icon (the copper "S" with a
"StripForge" wordmark, 2026-09-27), used as the KiCad Plugin and Content Manager icon. The PCM
`metadata.json` schema has no icon field: the PCM takes the icon from `resources/icon.png` in the
package archive, and from an `icon.png` next to `metadata.json` in the metadata repository. The
The only toolbar icon is `plugins/icons/dialog-24.png` and `dialog-48.png`. Older letter-badge
icons are not shipped. The larger artwork (`assets/StripForge-icon-1024x1024.png`) is kept for reference.

See [CONTRIBUTING.md](CONTRIBUTING.md) and [CHANGELOG.md](CHANGELOG.md).

## Credits and prior art

- **[perfboard-studio](https://github.com/medinstech/perfboard-studio)** (Apache-2.0) inspired
  StripForge. Its stripboard model (strips split into segments at the cuts), connectivity checks
  and build guide shaped this design. Any code adapted from it will keep its attribution and
  Apache-2.0 notices, which is compatible with GPL-3.0.
- **[VeroRoute](https://sourceforge.net/projects/veroroute/)**, **VeeCAD** and
  **[DIYLC](https://github.com/bancika/diy-layout-creator)** are the standalone stripboard and
  layout tools that came before. They are credited for ideas only; no code is taken from them.

## License

Copyright (C) 2026 Somerled Design.

StripForge is free software: you can redistribute it and/or modify it under the terms of the
**GNU General Public License** as published by the Free Software Foundation, either **version 3** of
the License, or (at your option) **any later version** (`GPL-3.0-or-later`). It is distributed in
the hope that it will be useful, but WITHOUT ANY WARRANTY. See [LICENSE](LICENSE) for the full text.

## Author

**Somerled Design** ([@SomerledDesign](https://github.com/SomerledDesign))

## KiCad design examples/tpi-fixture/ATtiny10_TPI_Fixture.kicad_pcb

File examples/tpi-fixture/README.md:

# ATtiny10 TPI programming fixture (unit example)

Unit and regression tests still run on this board. It is not the circuit acceptance project.
That is `tests/fixtures/ledswitch25/LedSwitch25-kicad.zip` (sha256
`4b6641a48ca721d24437f30cdbdc85c4168e3854628f75778c3d98b421883e3c`). Do not point an acceptance
run at this folder or at an older LedSwitch zip.

This board is Kevin's ATtiny10 TPI programming fixture with the real parts chosen, placed by
Mildrew. The KiCad project lives outside this repo, in Dropbox at `KiCad/ATtiny10_TPI_Fixture`.

Files:

- `ATtiny10_TPI_Fixture.net`: the netlist, exported with
  `kicad-cli sch export netlist --format kicadsexpr` (Eeschema 10.0.4). 22 components, 41 nets.
- `ATtiny10_TPI_Fixture.kicad_pcb`: the board after *Update PCB from Schematic* (F8), saved by
  KiCad 10.0.4, with the 22 footprints (86 THT pads) placed on a 2.54 mm grid and no tracks.
  Parts include the MSS6200 ZIF adapter (SW1, 2×9), the SOT23-6 carrier (J2, 2×9), the IDC 2×5
  (J1), two SS12D00G slide switches (SW2, SW3, 2.50 mm pitch), a push button (SW4), the MPD
  BH23APC battery holder (BT1, slotted) and a Littelfuse 395 fuse (F1). Project-library
  footprints are embedded in the board, so the `.pretty` library is not needed here.
- The Edge.Cuts outline is (50, 50)–(192.24, 110.96) mm, Kevin's X56 board: 56 × 24 holes
  (`A1`–`X56`), the first hole half a pitch in, at (51.27, 51.27) mm. The parts sit in the left
  30 columns.

Use it with Kevin's X56 config ([../x56.toml](../x56.toml)), which lists `BT1` as slotted:

```sh
stripforge analyze examples/tpi-fixture/ATtiny10_TPI_Fixture.kicad_pcb \
    --netlist examples/tpi-fixture/ATtiny10_TPI_Fixture.net --config examples/x56.toml
```

All 22 parts snap (BT1 as two slot jobs on strip U), with 0 conflicts, and the X56 grid matches
the outline. `stripforge build` on it gives 59 cuts and proposes 25 wire links of the 39 needed;
13 nets can't be joined by vertical links with this placement (see the build report).

The earlier M1 version of this fixture (25 footprints, 36 nets) is frozen in
[tests/fixtures/tpi-m1](../../tests/fixtures/tpi-m1) for the M1 tests.

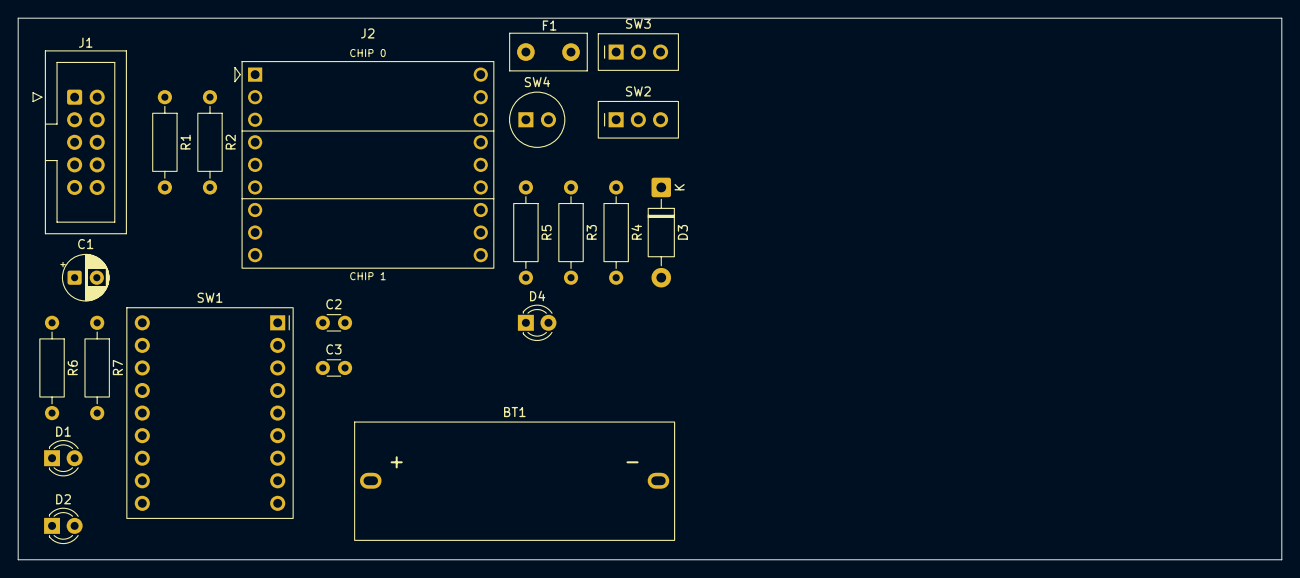
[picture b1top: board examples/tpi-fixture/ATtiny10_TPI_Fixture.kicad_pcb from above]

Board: 2 copper layers, 142.2 x 61.0 mm, 22 parts (0 on the bottom side), 24 nets, no tracks yet.

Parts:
BT1: 12V 23A cell (MPD BH23APC); BatteryHolder_MPD_BH23APC_1x23A_Stripboard_H0-H13
C1: 10uF 25V; CP_Radial_D5.0mm_P2.50mm
C2, C3: 100nF; C_Disc_D3.0mm_W1.6mm_P2.50mm
D1, D2: GREEN; LED_D3.0mm
D3: 1N4742A 12V 1W; D_DO-41_SOD81_P10.16mm_Horizontal
D4: RED; LED_D3.0mm
F1: PTC 100mA hold; Fuse_Littelfuse_395Series
J1: USBasp ISP (2x5 box header); IDC-Header_2x05_P2.54mm_Vertical
J2: CNV-SOT23-6L-DIP carrier; CNV-SOT23-6L-DIP_2x09_P2.54mm
R1, R2: 220; R_Axial_DIN0207_L6.3mm_D2.5mm_P10.16mm_Horizontal
R3, R6, R7: 1k; R_Axial_DIN0207_L6.3mm_D2.5mm_P10.16mm_Horizontal
R4: 22k; R_Axial_DIN0207_L6.3mm_D2.5mm_P10.16mm_Horizontal
R5: 4.7k; R_Axial_DIN0207_L6.3mm_D2.5mm_P10.16mm_Horizontal
SW1: CHIP SEL 6PDT (MSS6200 on adapter); MSS6200_Adapter_2x09_P2.54mm
SW2: MODE NORMAL/HV; SW_Slide_SPDT_SS12D00G_P2.50mm_Vertical
SW3: HV POWER; SW_Slide_SPDT_SS12D00G_P2.50mm_Vertical
SW4: HV ENABLE (guarded); SW_Push_Round_D6mm_1x02_P2.54mm_PROVISIONAL

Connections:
/SCHEMATIC DIAGRAM/+5V_T: C1.1, J1.2, SW1.2
/SCHEMATIC DIAGRAM/CLK0: J2.3, SW1.7
/SCHEMATIC DIAGRAM/CLK1: J2.9, SW1.9
/SCHEMATIC DIAGRAM/DAT0: J2.1, SW1.10
/SCHEMATIC DIAGRAM/DAT1: J2.7, SW1.12
/SCHEMATIC DIAGRAM/HV_RST: D3.1, R3.2, R4.1, SW2.3
/SCHEMATIC DIAGRAM/HV_SW: R3.1, R5.1, SW4.2
/SCHEMATIC DIAGRAM/MOSI: J1.1, R1.1
/SCHEMATIC DIAGRAM/PROG_RST: J1.5, SW2.1
/SCHEMATIC DIAGRAM/RESET_BUS: SW1.5, SW2.2
/SCHEMATIC DIAGRAM/RST0: J2.18, SW1.4
/SCHEMATIC DIAGRAM/RST1: J2.12, SW1.6
/SCHEMATIC DIAGRAM/SCK: J1.7, R2.1
/SCHEMATIC DIAGRAM/TPICLK: R2.2, SW1.8
/SCHEMATIC DIAGRAM/TPIDATA: R1.2, SW1.11
/SCHEMATIC DIAGRAM/VCC0: C2.1, J2.17, R6.1, SW1.1
/SCHEMATIC DIAGRAM/VCC1: C3.1, J2.11, R7.1, SW1.3
GND: BT1.2, C1.2, C2.2, C3.2, D1.1, D2.1, D3.2, D4.1, J1.4, J1.6, J1.8, J1.10, J2.2, J2.8, R4.2
unnamed: BT1.1, F1.1
unnamed: D1.2, R6.2
unnamed: D2.2, R7.2
unnamed: D4.2, R5.2
unnamed: SW3.1, SW4.1
unnamed: F1.2, SW3.2

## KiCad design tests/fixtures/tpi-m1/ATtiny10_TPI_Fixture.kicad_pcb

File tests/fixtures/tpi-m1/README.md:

# Frozen M1 TPI fixture

The ATtiny10 TPI fixture as committed in `cea21cd` (25 footprints, 36 nets, 82 THT pads): the
board and netlist that M1 and M2 part A were developed against. It is frozen here so the tests
that pin its exact numbers (cuts, hints, snap offsets) stay stable. `examples/tpi-fixture/` now
holds the real-parts board (22 footprints, 41 nets). Grid config: `examples/stripboard.toml`.
Circuit acceptance uses `tests/fixtures/ledswitch25/LedSwitch25-kicad.zip`, not this fixture and
not an older LedSwitch archive.

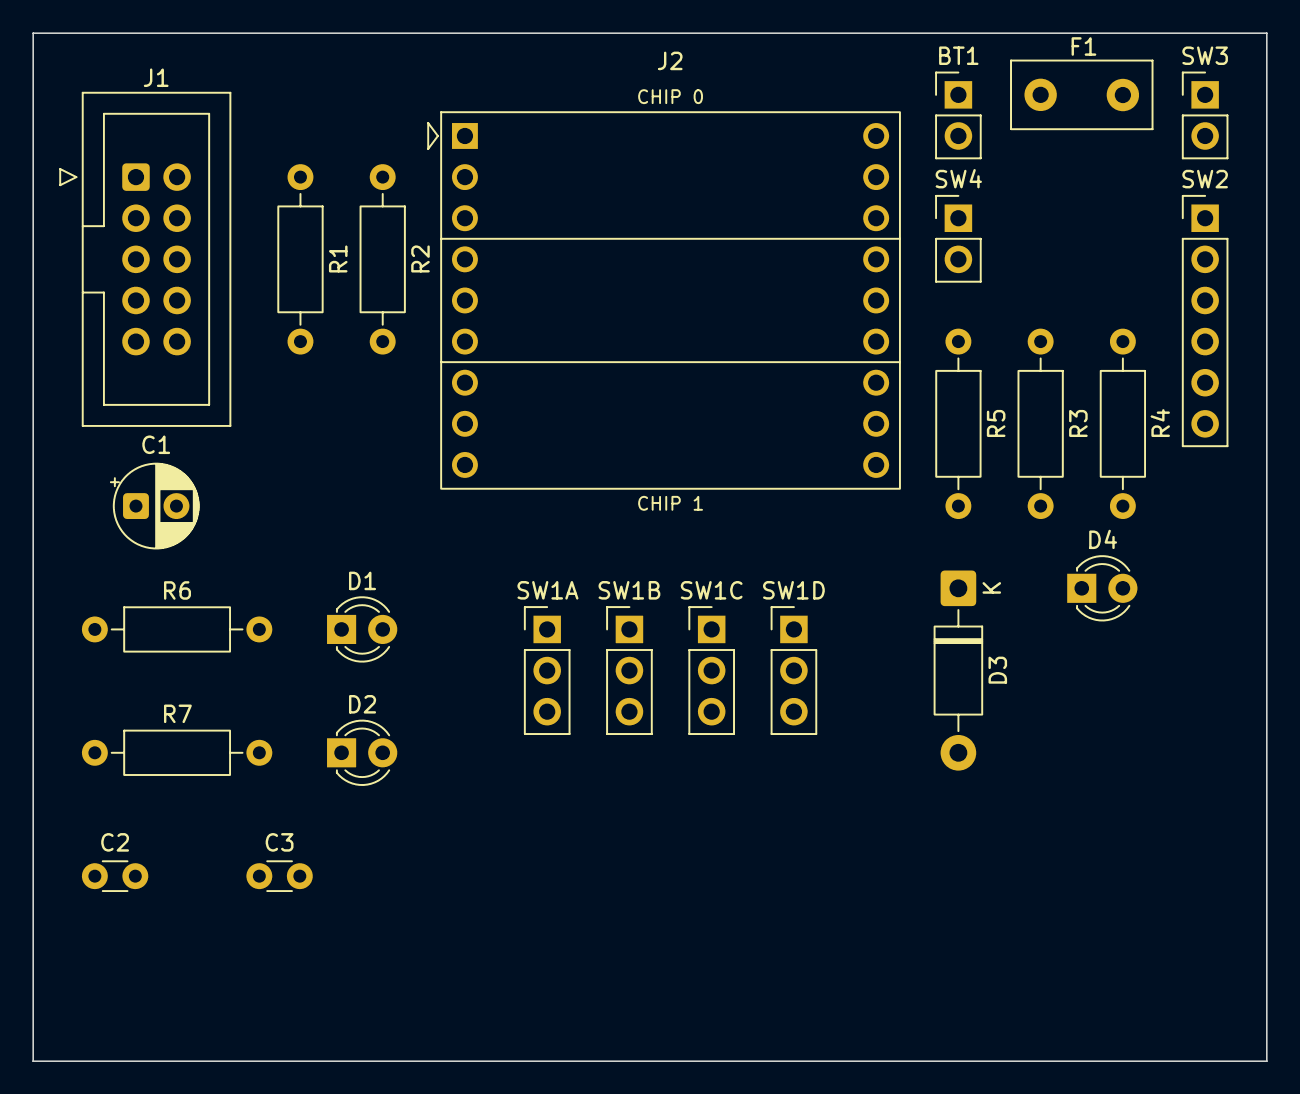
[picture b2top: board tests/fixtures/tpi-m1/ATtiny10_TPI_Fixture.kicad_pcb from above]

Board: 2 copper layers, 76.2 x 63.5 mm, 25 parts (0 on the bottom side), 25 nets, no tracks yet.

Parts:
BT1: 12V (23A or 8xAA pack); PinHeader_1x02_P2.54mm_Vertical
C1: 10uF 25V; CP_Radial_D5.0mm_P2.50mm
C2, C3: 100nF; C_Disc_D3.0mm_W1.6mm_P2.50mm
D1, D2: GREEN; LED_D3.0mm
D3: 1N4742A 12V 1W; D_DO-41_SOD81_P10.16mm_Horizontal
D4: RED; LED_D3.0mm
F1: PTC 100mA hold; Fuse_Littelfuse_395Series
J1: USBasp ISP (2x5 box header); IDC-Header_2x05_P2.54mm_Vertical
J2: CNV-SOT23-6L-DIP carrier; CNV-SOT23-6L-DIP_2x09_P2.54mm
R1, R2: 220; R_Axial_DIN0207_L6.3mm_D2.5mm_P10.16mm_Horizontal
R3, R6, R7: 1k; R_Axial_DIN0207_L6.3mm_D2.5mm_P10.16mm_Horizontal
R4: 22k; R_Axial_DIN0207_L6.3mm_D2.5mm_P10.16mm_Horizontal
R5: 4.7k; R_Axial_DIN0207_L6.3mm_D2.5mm_P10.16mm_Horizontal
SW1A: 4PDT on-on (pole A); PinHeader_1x03_P2.54mm_Vertical
SW1B: 4PDT on-on (pole B); PinHeader_1x03_P2.54mm_Vertical
SW1C: 4PDT on-on (pole C); PinHeader_1x03_P2.54mm_Vertical
SW1D: 4PDT on-on (pole D); PinHeader_1x03_P2.54mm_Vertical
SW2: MODE NORMAL/HV; PinHeader_1x06_P2.54mm_Vertical
SW3: HV POWER; PinHeader_1x02_P2.54mm_Vertical
SW4: HV ENABLE (guarded); PinHeader_1x02_P2.54mm_Vertical

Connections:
/SCHEMATIC DIAGRAM/+5V_T: C1.1, J1.2, SW1A.2
/SCHEMATIC DIAGRAM/CLK0: J2.3, SW1C.1
/SCHEMATIC DIAGRAM/CLK1: J2.9, SW1C.3
/SCHEMATIC DIAGRAM/DAT0: J2.1, SW1D.1
/SCHEMATIC DIAGRAM/DAT1: J2.7, SW1D.3
/SCHEMATIC DIAGRAM/HV_ARMED: R3.1, SW2.6
/SCHEMATIC DIAGRAM/HV_RST: D3.1, R3.2, R4.1, SW2.3
/SCHEMATIC DIAGRAM/HV_SW: R5.1, SW2.5, SW4.2
/SCHEMATIC DIAGRAM/MOSI: J1.1, R1.1
/SCHEMATIC DIAGRAM/PROG_RST: J1.5, SW2.1
/SCHEMATIC DIAGRAM/RESET_BUS: SW1B.2, SW2.2
/SCHEMATIC DIAGRAM/RST0: J2.18, SW1B.1
/SCHEMATIC DIAGRAM/RST1: J2.12, SW1B.3
/SCHEMATIC DIAGRAM/SCK: J1.7, R2.1
/SCHEMATIC DIAGRAM/TPICLK: R2.2, SW1C.2
/SCHEMATIC DIAGRAM/TPIDATA: R1.2, SW1D.2
/SCHEMATIC DIAGRAM/VCC0: C2.1, J2.17, R6.1, SW1A.1
/SCHEMATIC DIAGRAM/VCC1: C3.1, J2.11, R7.1, SW1A.3
GND: BT1.2, C1.2, C2.2, C3.2, D1.1, D2.1, D3.2, D4.1, J1.4, J1.6, J1.8, J1.10, J2.2, J2.8, R4.2
unnamed: BT1.1, F1.1
unnamed: D1.2, R6.2
unnamed: D2.2, R7.2
unnamed: D4.2, R5.2
unnamed: F1.2, SW3.1
unnamed: SW3.2, SW4.1

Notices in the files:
README.md:
License: GPL-3.0-or-later
